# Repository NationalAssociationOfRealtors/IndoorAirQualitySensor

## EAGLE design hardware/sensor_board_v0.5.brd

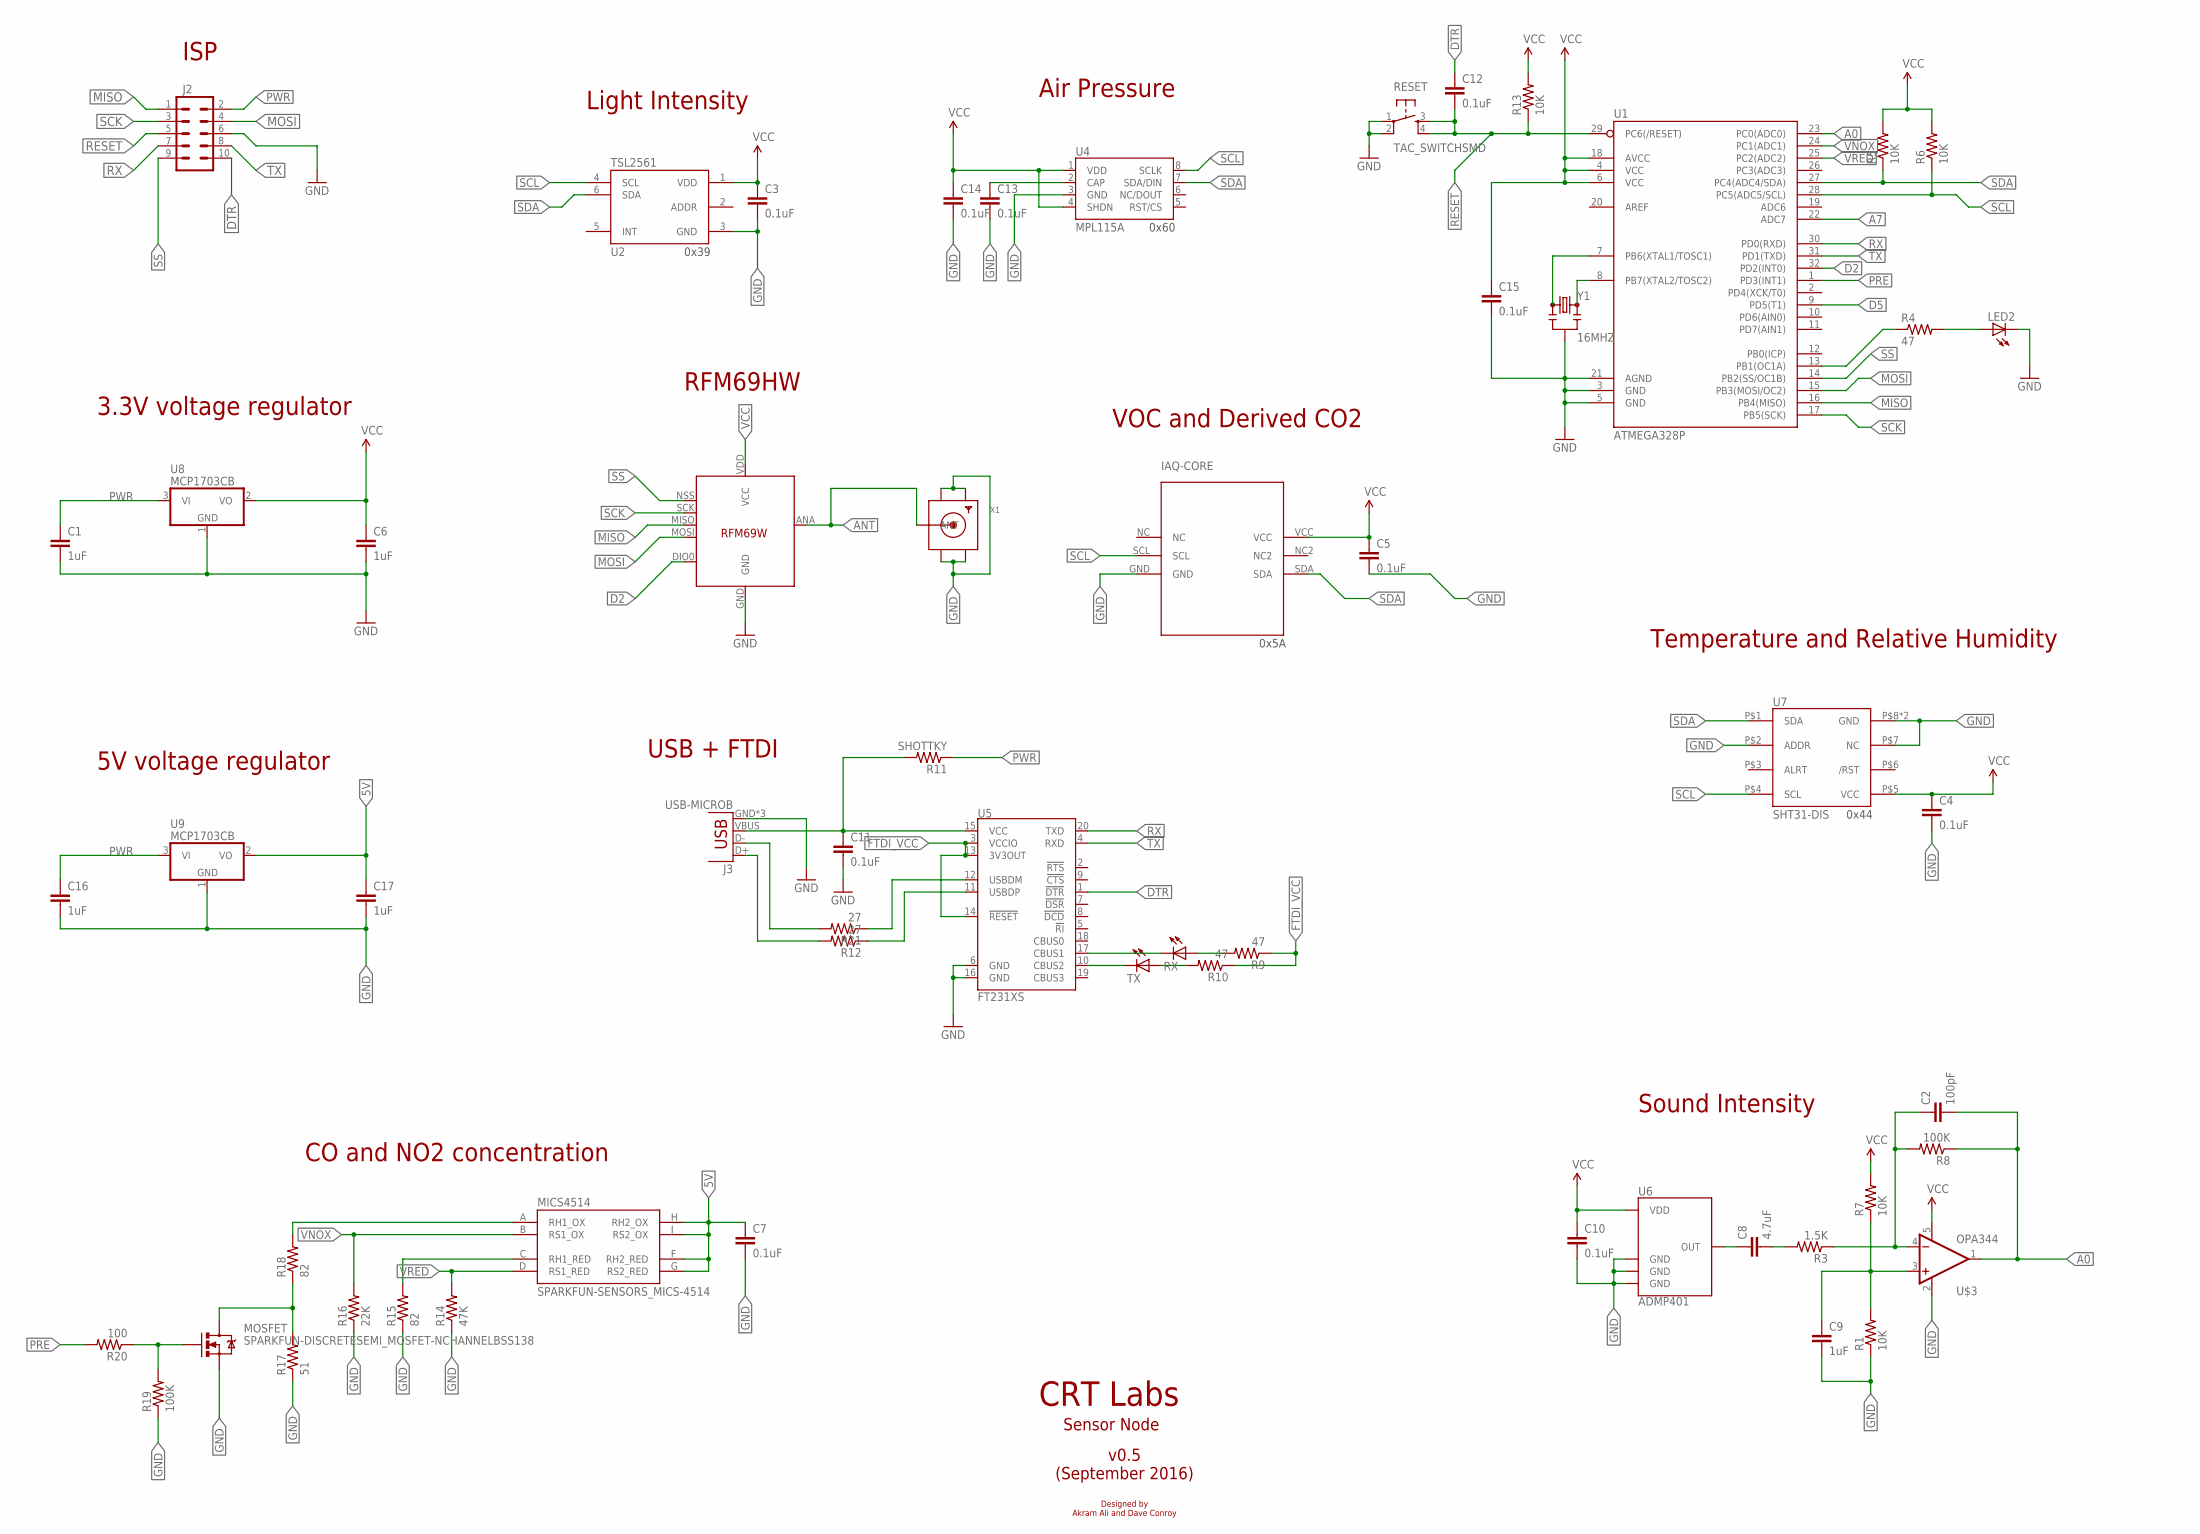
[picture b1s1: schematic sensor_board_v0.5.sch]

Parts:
C1, C6, C9, C16, C17: 1uF; 0805
C2: 100pF; 0805
C3, C4, C5, C7, C10, C11, C12, C13, C14, C15: 0.1uF; 0805
C8: 4.7uF; 0805
IAQ-CORE: IAQ-CORE; MPN IAQ CORE
J2: M05X2PTH; AVR_ICSP
J3: USB-MICROB
LED2: LEDCHIPLED_0805; CHIPLED_0805
MICS4514: SPARKFUN-SENSORS_MICS-4514; SPARKFUN-SENSORS_MICS_10-SMD
MOSFET: SPARKFUN-DISCRETESEMI_MOSFET-NCHANNELBSS138; SPARKFUN-DISCRETESEMI_SOT23-3
R1, R5, R6, R7, R13: 10K; 0805
R3: 1.5K; 0805
R4, R9, R10: 47; 0805
R8, R19: 100K; 0805
R11: SHOTTKY; 0805
R12, R21: 27; 0805
R14: 47K; 0805
R15, R18: 82; 0805
R16: 22K; 0805
R17: 51; 0805
R20: 100; 0805
RESET: TAC_SWITCHSMD; TACTILE-SWITCH-SMD
RX: LEDCHIPLED_0805; CHIPLED_0805
TX: LEDCHIPLED_0805; CHIPLED_0805
U1: ATMEGA328P; TQFP32-08; MPN ATMEGA328PB-AU
U2: TSL2561; FN-6; MOUSER# 856-TSL2561T; DIGIKEY# TSL2561-FNCT-ND
U4: MPL115A; LGA8
U5: FT231XS; SSOP20_L
U6: ADMP401
U7: SHT31-DIS; SHT3X; MPN SHT31-DIS-B
U8, U9: MCP1703CB; SOT23; MPN MCP1703T-2502E/CB
U$3: OPA344; SOT23-5
U$4: RFM69HW; LOWPOWERLAB_RFM69W-MINPADS
X1: SMACONNECTOR_EDGE; SMA_EDGELAUNCH
Y1: 16MHZ; RESONATOR-SMD

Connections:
5V: C7.1, C17.1, MICS4514.F (RH2_RED), MICS4514.G (RS2_RED), MICS4514.H (RH2_OX), MICS4514.J (RS2_OX), U9.2 (VO)
A0: C2.2, R8.1, U1.23 (PC0(ADC0)), U$3.1 (OUT)
A7: U1.22 (ADC7)
ANT: U$4.ANA (ANT), X1.P (ANT)
D2: U1.32 (PD2(INT0)), U$4.DIO0
D5: U1.9 (PD5(T1))
DTR: C12.1, J2.10, U5.1 (!DTR)
FTDI_VCC: R9.1, R10.1, U5.3 (VCCIO), U5.13 (3V3OUT), U5.14 (!RESET)
GND: C1.2, C3.2, C4.2, C5.2, C6.2, C7.2, C9.2, C10.2, C11.2, C13.2, C14.2, C15.2, C16.2, C17.2, IAQ-CORE.GND, J2.6, J3.GND, J3.MT1 (GND), J3.MT2 (GND), LED2.C, MOSFET.2 (S), R1.1, R14.1, R15.1, R16.1, R17.1, R19.1, RESET.1, RESET.2, U1.3 (GND), U1.5 (GND), U1.21 (AGND), U2.3 (GND), U4.3 (GND), U5.6 (GND), U5.16 (GND), U6.2 (GND), U6.4 (GND), U6.6 (GND), U7.P$2 (ADDR), U7.P$7 (NC), U7.P$8 (GND), U7.PAD (GND), U8.1 (GND), U9.1 (GND), U$3.2 (V-), U$4.GND, X1.GND@1 (GND4), X1.GND@2 (GND3), X1.GND@3 (GND2), X1.GND@4 (GND1), Y1.2
MISO: J2.1, U1.16 (PB4(MISO)), U$4.MISO
MOSI: J2.4, U1.15 (PB3(MOSI/OC2)), U$4.MOSI
unnamed: R4.1, U1.13 (PB1(OC1A))
unnamed: LED2.A, R4.2
unnamed: U1.8 (PB7(XTAL2/TOSC2)), Y1.3
unnamed: U1.7 (PB6(XTAL1/TOSC1)), Y1.1
unnamed: C8.1, U6.1 (OUT)
unnamed: MICS4514.A (RH1_OX), R18.2
unnamed: C8.2, R3.2
unnamed: C2.1, R3.1, R8.2, U$3.4 (-IN)
unnamed: C9.1, R1.2, R7.1, U$3.3 (+IN)
unnamed: C13.1, U4.2 (CAP)
unnamed: MICS4514.C (RH1_RED), R15.2
unnamed: RX.C, U5.17 (CBUS1)
unnamed: TX.C, U5.10 (CBUS2)
unnamed: MOSFET.3 (D), R17.2, R18.1
unnamed: MOSFET.1 (G), R19.2, R20.1
unnamed: R21.1, U5.12 (USBDM)
unnamed: R12.1, U5.11 (USBDP)
unnamed: R9.2, RX.A
unnamed: R10.2, TX.A
unnamed: J3.D-, R21.2
unnamed: J3.D+, R12.2
PRE: R20.2, U1.1 (PD3(INT1))
PWR: C1.1, C16.1, J2.2, R11.1, U8.3 (VI), U9.3 (VI)
RESET: C12.2, J2.5, R13.1, RESET.3, RESET.4, U1.29 (PC6(/RESET))
RX: J2.7, U1.30 (PD0(RXD)), U5.20 (TXD)
SCK: J2.3, U1.17 (PB5(SCK)), U$4.SCK
SCL: IAQ-CORE.SCL, R6.1, U1.28 (PC5(ADC5/SCL)), U2.4 (SCL), U4.8 (SCLK), U7.P$4 (SCL)
SDA: IAQ-CORE.SDA, R5.1, U1.27 (PC4(ADC4/SDA)), U2.6 (SDA), U4.7 (SDA/DIN), U7.P$1 (SDA)
SS: J2.9, U1.14 (PB2(SS/OC1B)), U$4.NSS (SEL)
TX: J2.8, U1.31 (PD1(TXD)), U5.4 (RXD)
VBUS: C11.1, J3.VBUS, R11.2, U5.15 (VCC)
VCC: C3.1, C4.1, C5.1, C6.1, C10.1, C14.1, C15.1, IAQ-CORE.VCC, R5.2, R6.2, R7.2, R13.2, U1.4 (VCC), U1.6 (VCC), U1.18 (AVCC), U2.1 (VDD), U4.1 (VDD), U4.4 (SHDN), U6.5 (VDD), U7.P$5 (VCC), U8.2 (VO), U$3.5 (V+), U$4.VDD (VCC)
VNOX: MICS4514.B (RS1_OX), R16.2, U1.24 (PC1(ADC1))
VRED: MICS4514.D (RS1_RED), R14.2, U1.25 (PC2(ADC2))

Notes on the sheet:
Light Intensity
VOC and Derived CO2
Air Pressure
Sound Intensity
Temperature and Relative Humidity
ISP
3.3V voltage regulator
CO and NO2 concentration
CRT Labs
Sensor Node
v0.5 (September 2016)
Designed by Akram Ali and Dave Conroy
5V voltage regulator
RFM69HW
USB + FTDI
0x39
0x60
0x5A
0x44

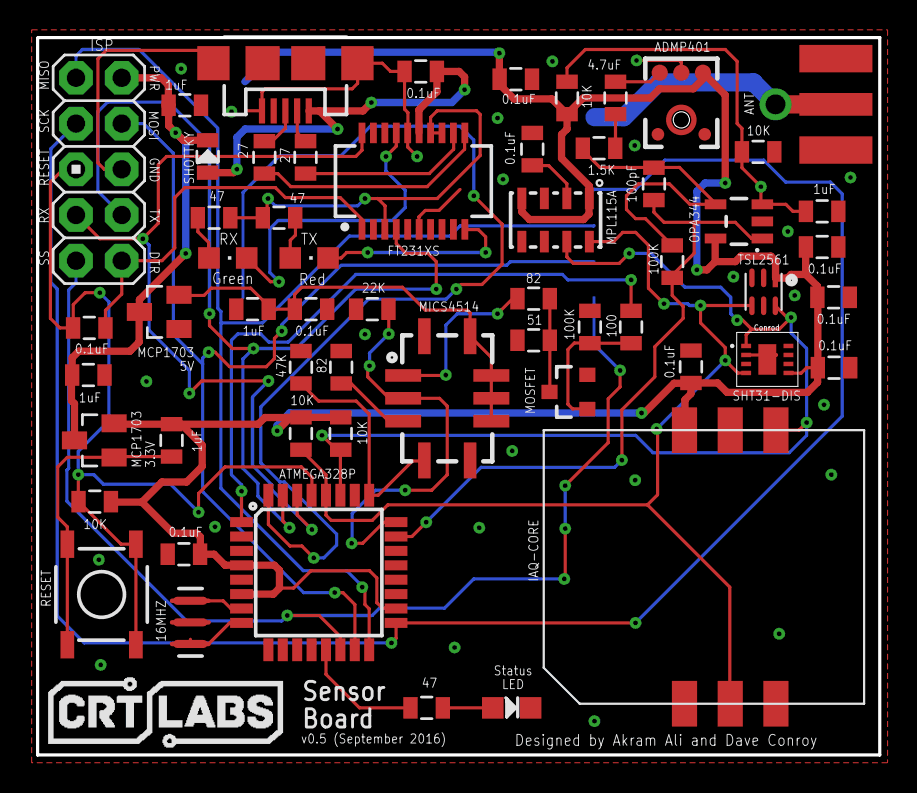
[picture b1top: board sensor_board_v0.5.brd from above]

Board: 2 copper layers, 46.8 x 39.9 mm, 58 parts (1 on the bottom side), 43 nets.

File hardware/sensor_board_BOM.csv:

Qty,Value,Device,Package,Parts,DIGIKEY#,MANF,MANF#,MOUSER#,MPN,OC_NEWARK,PROD_ID,VALUE,Description
1,1.5K,RESISTOR0805-RES,805,R3,YAG1814CT-ND,Yageo,RT0805BRD071K5L,603-RT0805BRD071K5L,RT0805BRD071K5L,unknown,,,Resistor
1,100,RESISTOR0805-RES,805,R20,311-100CRCT-NDE,,RC0805FR-07100RL,603-RC0805FR-07100RL,RC0805FR-07100RL,unknown,,,Resistor
1,100pF,CAP0805,805,C2,311-1111-1-ND,,CC0805JRNPO9BN101,603-CC805JRNPO9BN101,CC0805JRNPO9BN101,unknown,,,Capacitor
1,10K,RESISTOR0805-RES,805,R13,311-10KARCT-ND,Yageo,RC0805JR-0710KL,603-RC0805JR-0710KL,RC0805JR-0710KL,,,,Resistor
1,16MHZ,RESONATOR16MHZ,RESONATOR-SMD,Y1,490-1198-1-ND,,CSTCE16M0V53-R0,81-CSTCE16M0V53-R0,CSTCE16M0V53-R0,unknown,XTAL-08900,16MHZ,Resonator
1,22K,RESISTOR0805-RES,805,R16,311-22KARCT-NDE,,RC0805JR-0722KL,603-RC0805JR-0722KL,RC0805JR-0722KL,unknown,,,Resistor
1,4.7uF,CAP0805,805,C8,311-1871-1-ND,,CC0805KKX5R8BB475,603-CC805KKX5R8BB475,CC0805KKX5R8BB475,unknown,,,Capacitor
1,47K,RESISTOR0805-RES,805,R14,RHM47KKCT-ND,Rohm Semiconductor,ESR10EZPJ473,755-ESR10EZPJ473,ESR10EZPJ473,unknown,,,Resistor
1,51,RESISTOR0805-RES,805,R17,RHM51KCT-ND,Rohm Semiconductor,ESR10EZPJ510,755-ESR10EZPJ510,ESR10EZPJ510,unknown,,,Resistor
1,ADMP401,ADMP401,ADMP401,U6,INMP401ACEZ-R7CT-ND,,INMP401ACEZ-R7,N/A,INMP401ACEZ-R7,,,,Omnidirection bottom-port MEMS microphone
1,ATMEGA328P,ATMEGA328P_TQFP,TQFP32-08,U1,ATMEGA328P-AU-ND,Atmel,ATMEGA328P-AU,556-ATMEGA328P-AU,ATMEGA328P-AU,58Y6083,IC-09069,ATMEGA328P_TQFP,
1,FT231XS,FT231XS,SSOP20_L,U5,768-1129-1-ND,FTDI,FT231XS-R,895-FT231XS-R,FT231XS-R,,IC-11524,FT231XS,FTDI FT231X Full Speed USB to Full-handshake UART
1,IAQ-CORE,IAQ-CORE,IAQ-CORE,IAQ-CORE,IAQ-CORE C-ND,ams,IAQ-CORE C,985-IAQ-COREC,IAQ-CORE C,82Y5455,,,
1,MPL115A,MPL115A,LGA8,U4,MPL115A2-ND,Freescale Semiconductor - NXP,MPL115A2,841-MPL115A2,MPL115A2,,,,MPL115A1 (SPI) and MPL115A2 (I2C) Miniature Digital Barometer
1,OPA344,OPA344,SOT23-5,U$3,296-41475-1-ND,Texas Instruments,OPA344NA/3K,595-OPA344NA/3K,OPA344NA/3K,,IC-08251,,Single gate rail-to-rail output op-amp. Inputs extend 300mV past rails.
,,,,,,,,,,,,,
1,SHOTTKY,RESISTOR0805-RES,805,R11,478-7799-1-ND,AVX,SD0805S020S0R5,581-SD0805S020S0R5,SD0805S020S0R5,unknown,,,Resistor
1,SHT31-DIS,SHT31-DIS,SHT3X,U7,1649-1011-1-ND,,SHT31-DIS-B,403-SHT31-DIS-B,SHT31-DIS-B,47Y1304,,,
1,TAC_SWITCHSMD,TAC_SWITCHSMD,TACTILE-SWITCH-SMD,RESET,CKN9104CT-ND,C&K Components,PTS525SM15SMTR2 LFS,611-PTS525SM15SMTR2,PTS525SM15SMTR2 LFS,,SWCH-08247,TAC_SWITCHSMD,Momentary Switch
1,TSL2561,TSL2561FN,FN-6,U2,TSL2561-FNCT-ND,AMS-TAOS-USA-Inc.,TSL2561FN,856-TSL2561T,TSL2561FN,82Y5564,IC-11791,,TSL2561 illumination sensor
1,USB-MICROB,USB-MICROB,USB-MICROB,J3,,,,,,,CONN-09505,,USB Connectors
2,100K,RESISTOR0805-RES,805,R8,311-100KCRCT-NDE,Yageo,RC0805FR-07100KL,603-RC0805FR-07100KL,RC0805FR-07100KL,,,,
2,27,RESISTOR0805-RES,805,R12,,Yageo,RC0603JR-0727RL,603-RC0603JR-0727RL,RC0603JR-0727RL,,,,
2,82,RESISTOR0805-RES,805,R15,541-82.0CCT-NDE,,CRCW080582R0FKEA,71-CRCW0805-82-E3,CRCW080582R0FKEA,,,,
2,MCP1703CB,MCP1703CB,SOT23,U8,MCP1703T-3302E/CBCT-ND,,MCP1703T-3302E/CB,579-MCP1703T-3302ECB,MCP1703T-3302E/CB,,,,
3,,LEDCHIPLED_0805,CHIPLED_0805,LED2,LED,LED,LED,LED,LED,LED,LED,LED,LED
3,47,RESISTOR0805-RES,805,R4,311-47ARCT-ND,,RC0805JR-0747RL,603-RC0805JR-0747RL,RC0805JR-0747RL,,,,
4,0.1uF,CAP0805,805,C12,311-1088-1-ND,,CC0603KRX7R7BB104,603-CC603KRX7R7BB104,CC0603KRX7R7BB104,,,,
4,10K,RESISTOR0805-RES,805,R1,311-10KARCT-ND,Yageo,RC0805JR-0710KL,603-RC0805JR-0710KL,RC0805JR-0710KL,,,,
5,1uF,CAP0805,805,C1,311-1365-1-ND,,CC0805KKX7R7BB105,603-CC805KKX7R7BB105,CC0805KKX7R7BB105,,,,
6,0.1uF,CAP0805,805,C3,311-1088-1-ND,,CC0603KRX7R7BB104,603-CC603KRX7R7BB104,CC0603KRX7R7BB104,,,,
,,,,,,,,,,,,,
,,,,,,,,,,,,,
,,,,,,,,,,,,,
Optional,,,,,,,,,,,,,
1,,M05X2PTH,AVR_ICSP,J2,,,,,0,,,,Header 5x2
1,,SMACONNECTOR_EDGE,SMA_EDGELAUNCH,X1,,,,,,,,,SMA Connector
1,SPARKFUN-DISCRETESEMI_MOSFET-NCHANNELBSS138,SPARKFUN-DISCRETESEMI_MOSFET-NCHANNELBSS138,SPARKFUN-DISCRETESEMI_SOT23-3,MOSFET,,,,,,,TRANS-00830,,Common NMOSFET Parts
1,SPARKFUN-SENSORS_MICS-4514,SPARKFUN-SENSORS_MICS-4514,SPARKFUN-SENSORS_MICS_10-SMD,MICS4514,,,,,,,COMP-12310,,Metal oxide MEMS carbon monoxide (CO) and NOx sensor in an SMD package.
1,RFM69HW,LOWPOWERLAB_RFM69,LOWPOWERLAB_RFM69W-MINPADS,U$4,,,,,,,,,

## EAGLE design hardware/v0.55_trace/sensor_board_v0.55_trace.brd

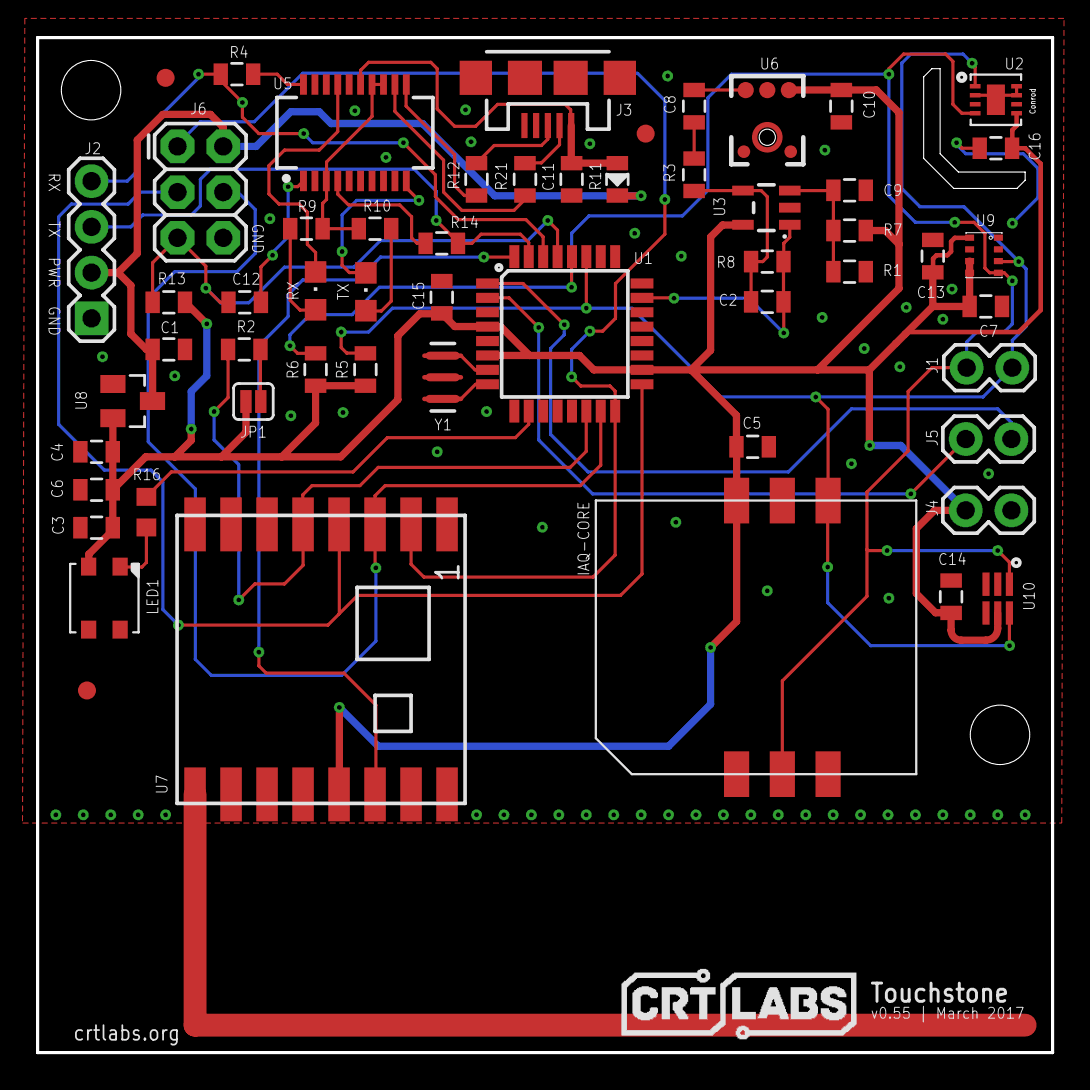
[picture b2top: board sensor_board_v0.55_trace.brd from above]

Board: 2 copper layers, 56.4 x 56.4 mm, 58 parts (0 on the bottom side), 38 nets.

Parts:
C1, C3, C9: 1uF; 0805
C2: 100pF; 0805
C4: 10uF; 0805
C5, C6, C7, C10, C11, C12, C13, C14, C15, C16: 0.1uF; 0805
C8: 4.7uF; 0805
H1, H2: STAND-OFF
IAQ-CORE: IAQ-CORE
J1, J4, J5: 1X02
J2: 1X04
J3: USB-MICROB
J6: AVR_SPI_PRG_6PTH; 2X3
JP1: JUMPER-PAD-2-NC_BY_PASTEFULL-BOX-SILK; PAD-JUMPER-2-NC_BY_PASTE_YES_SILK_FULL_BOX
LED1: WS2812B3535; LED3535
R1, R2, R5, R6, R7, R13: 10K; 0805
R3: 1.5K; 0805
R4, R14: 1K; 0805
R8: 100K; 0805
R9, R10: 47; 0805
R11: SHOTTKY; 0805
R12, R21: 27; 0805
R16: 470; R0603
RX: CHIPLED_0805
TX: CHIPLED_0805
U1: ATMEGA328P; TQFP32-08
U2: SHT35; SHT3X
U3: OPA344; SOT23-5
U5: FT231XS; SSOP20_L
U6: ADMP401
U7: RFM69HCW; RFM69HCW-XXXS2
U8: MCP1703CB; SOT23
U9: BMP280
U10: TSL2591; DFN6_TAOS
U$1, U$2, U$3: FIDUCIAL; FIDUCIAL_1MM
Y1: 16MHZ; RESONATOR-SMD

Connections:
A0: C2.2, R8.1, U1.23, U3.1
D2: U1.32, U7.14
D3: J5.2, U1.1
D4: J5.1, U1.2
D6: R16.2, U1.10
DTR: C12.1, U5.1
FTDI_VCC: R9.1, R10.1, U5.3, U5.13, U5.14
GND: C1.2, C3.2, C4.2, C5.2, C6.2, C7.2, C9.2, C10.2, C11.2, C13.2, C14.1, C15.2, C16.2, IAQ-CORE.GND, J2.1, J3.GND, J3.MT1, J3.MT2, J4.1, J6.6, LED1.4, R1.1, U1.3, U1.5, U1.21, U2.2, U2.7, U2.8, U2.THERMAL, U3.2, U5.6, U5.16, U6.2, U6.4, U6.6, U7.1, U7.8, U7.10, U8.1, U9.1, U9.7, U10.3, Y1.2
MISO: J6.1, U1.16, U7.2
MOSI: J6.4, U1.15, U7.3
unnamed: JP1.1, R2.2
unnamed: R14.2, U5.4
unnamed: R4.2, U5.20
unnamed: U1.8, Y1.3
unnamed: U1.7, Y1.1
unnamed: LED1.1, R16.1
unnamed: C8.2, R3.2
unnamed: C2.1, R3.1, R8.2, U3.4
unnamed: C9.1, R1.2, R7.1, U3.3
unnamed: RX.C, U5.17
unnamed: TX.C, U5.10
unnamed: R21.1, U5.12
unnamed: R12.1, U5.11
unnamed: R9.2, RX.A
unnamed: R10.2, TX.A
unnamed: J3.D-, R21.2
unnamed: J3.D+, R12.2
OUT: C8.1, U6.1
PWR: C1.1, J2.2, J6.2, R11.1, U8.3
RESET: C12.2, J6.5, R13.1, U1.29
RX: J2.4, R4.1, U1.30
SCK: J6.3, U1.17, U7.4
SCL: IAQ-CORE.SCL, J1.1, R6.1, U1.28, U2.4, U9.4, U10.1
SDA: IAQ-CORE.SDA, J1.2, R5.1, U1.27, U2.1, U9.3, U10.6
SS: R2.1, U1.14, U7.5
TX: J2.3, R14.1, U1.31
VBUS: C11.1, J3.VBUS, R11.2, U5.15
VCC: C3.1, C4.1, C5.1, C6.1, C7.1, C10.1, C13.1, C14.2, C15.1, C16.1, IAQ-CORE.VCC, J4.2, JP1.2, LED1.2, R5.2, R6.2, R7.2, R13.2, U1.4, U1.6, U1.18, U2.5, U3.5, U6.5, U7.13, U8.2, U9.5, U9.6, U9.8, U10.5

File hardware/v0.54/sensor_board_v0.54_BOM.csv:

Qty,Value,Device,Package,Parts,Description,MPN
1,USB-MICROB,USB-MICROB,USB-MICROB,J3,USB Connectors,47346-0001
1,ATMEGA328P,ATMEGA328P_TQFP,TQFP32-08,U1,ATMEGA328P,ATMEGA328PB-AU
1,BMP280,BMP280,BMP280,U9,The BMP280 is an absolute barometric pressure sensor especially designed for mobile applications. The sensor module is housed in an extremely compact 8-pin metal-lid LGA package with a footprint of only 2.0 ÌÑ 2.5 mm2 and 0.95 mm package height. Its small,BMP280
1,100pF,CAP0805,805,C2,Capacitor,CC0805JRNPOABN101
1,10uF,CAP0805,805,C4,Capacitor,CC0805KKX5R6BB106
1,4.7uF,CAP0805,805,C8,Capacitor,CC0805KKX7R6BB475
10,0.1uF,CAP0805,805,C5-C6-C7-C10-C11-C12-C13-C14-C15-C16,Capacitor,CC0805KRX7R9BB104
3,1uF,CAP0805,805,C1-C3-C9,Capacitor,CC0805ZRY5V8BB105
1,16MHZ,RESONATOR16MHZ,RESONATOR-SMD,Y1,Resonator,CSTCE16M0V53-R0
1,FT231XS,FT231XS,SSOP20_L,U5,FTDI FT231X Full Speed USB to Full-handshake UART,FT231XQ-R
1,IAQ-CORE,IAQ-CORE,IAQ-CORE,IAQ-CORE,IAQ-CORE,IAQ-CORE C
1,ADMP401,ADMP401,ADMP401,U6,Omnidirection bottom-port MEMS microphone,INMP401ACEZ-R7
2,,LEDCHIPLED_0805,CHIPLED_0805,RX- TX,LED,LG R971-KN-1
1,MCP1703CB,MCP1703CB,SOT23,U8,250 mA- 16V- Low Quiescent Current LDO Regulator,MCP1703T-2502E/CB
1,OPA344,OPA344,SOT23-5,U3,Single gate rail-to-rail output op-amp. Inputs extend 300mV past rails.,OPA344NA/3K
1,100K,RESISTOR0805-RES,805,R8,Resistor,RC0805FR-07100KL 
6,10K,RESISTOR0805-RES,805,R1-R2-R5-R6-R7-R13,Resistor,RC0805FR-0710KL
1,1.5K,RESISTOR0805-RES,805,R3,Resistor,RC0805FR-071K5L 
2,1K,RESISTOR0805-RES,805,R4-R14,Resistor,RC0805FR-071KL
2,27,RESISTOR0805-RES,805,R12-R21,Resistor,RC0805FR-0727RL 
1,470,R-US_R0603,R0603,R16,RESISTOR- American symbol,RC0805FR-07470RL 
2,47,RESISTOR0805-RES,805,R9-R10,Resistor,RC0805FR-0747RL 
1,RFM69HW,LOWPOWERLAB_RFM69,LOWPOWERLAB_RFM69W-MINPADS,U4,RFM Radio,RFM69HW
1,SHOTTKY,RESISTOR0805-RES,805,R11,Resistor,SD0805S040S0R5
1,SHT35,SHT3X,SHT3X,U2,SHT3x - Digital Temperature and Humidity Sensor,SHT35-DIS-B
1,WS2812B3535,WS2812B3535,LED3535,LED1,LED,SK6812 mini
1,TSL2591,LIGHT_TSL2591,DFN6_TAOS,U10,TSL2591 Light-To-Digital Sensor,TSL25911FN

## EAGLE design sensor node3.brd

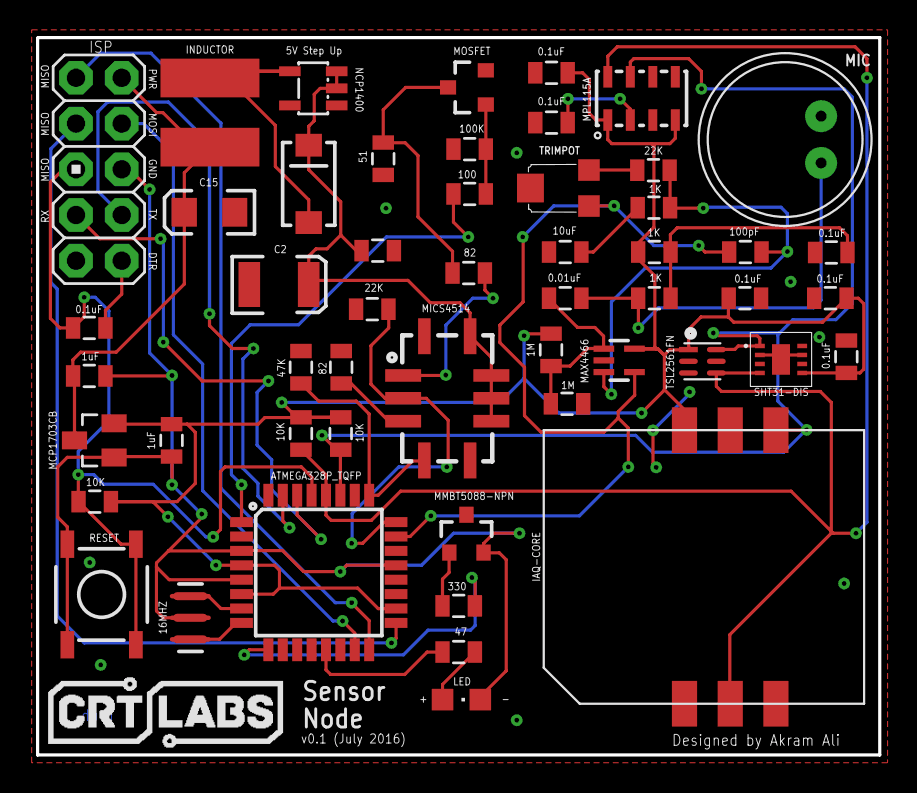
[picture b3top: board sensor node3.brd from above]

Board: 2 copper layers, 46.8 x 39.9 mm, 52 parts (0 on the bottom side), 36 nets.

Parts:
C1, C6: 1uF; 0805
C2: EIA3528
C3, C4, C5, C7, C9, C12, C13, C14: 0.1uF; 0805
C8: 0.01uF; 0805
C10: 10uF; 0805
C11: 100pF; 0805
C15: EIA3216
D1: SMA-DIODE
IAQ-CORE: IAQ-CORE
IC1: MCP1703CB; SOT23
INDUCTOR: CR54
J2: AVR_ICSP
LED2: CHIPLED_0805
MIC: ELECTRET_9.7
MICS4514: SPARKFUN-SENSORS_MICS-4514; SPARKFUN-SENSORS_MICS_10-SMD
MOSFET: SPARKFUN-DISCRETESEMI_MOSFET-NCHANNELBSS138; SPARKFUN-DISCRETESEMI_SOT23-3
NCP1400: SOT23-5
Q1: MMBT5088-NPN; SOT23-3
R2: 330; 0805
R4: 47; 0805
R5, R6, R13: 10K; 0805
R7, R8: 1M; 0805
R9, R10, R11: 1K; 0805
R12, R16: 22K; 0805
R14: 47K; 0805
R15, R18: 82; 0805
R17: 51; 0805
R19: 100K; 0805
R20: 100; 0805
RESET: TAC_SWITCHSMD; TACTILE-SWITCH-SMD
TRIMPOT: TRIMPOT_BOURNS_TC33X-2
U1: ATMEGA328P_TQFP; TQFP32-08
U2: TSL2561FN; FN-6
U3: SC70-5
U4: MPL115A; LGA8
U$1: SHT31-DIS; SHT3X
Y1: 16MHZ; RESONATOR-SMD

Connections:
5V: C2.A, C7.1, D1.C, MICS4514.F, MICS4514.G, MICS4514.H, MICS4514.J, NCP1400.2, NCP1400.3
A0: C11.2, TRIMPOT.1, U1.23, U3.4
D5: R2.1, U1.9
DTR: C12.1, J2.10
GND: C1.2, C6.2, IC1.1, J2.6, LED2.C, Q1.2, RESET.1, RESET.2, U1.3, U1.5, U1.21, Y1.2
GND0: C2.C, C3.2, C4.2, C5.2, C7.2, C9.2, C10.2, C13.2, C14.2, C15.C, IAQ-CORE.GND, MIC.-, MOSFET.2, NCP1400.5, Q1.3, R8.1, R14.1, R15.1, R16.1, R17.1, R19.1, U2.3, U3.2, U4.3, U$1.P$2, U$1.P$7, U$1.P$8, U$1.PAD
MISO: J2.1, U1.16
MOSI: J2.4, U1.15
unnamed: Q1.1, R2.2
unnamed: R4.1, U1.13
unnamed: LED2.A, R4.2
unnamed: U1.8, Y1.3
unnamed: U1.7, Y1.1
unnamed: C8.2, R7.1, R8.2, U3.1
unnamed: C11.1, R11.2, R12.1, U3.3
unnamed: MICS4514.A, R18.2
unnamed: C8.1, MIC.+, R9.1
unnamed: C9.1, R9.2, R10.1
unnamed: C13.1, U4.2
unnamed: MICS4514.C, R15.2
unnamed: C10.1, R11.1
unnamed: R12.2, TRIMPOT.3
unnamed: D1.A, INDUCTOR.P$2, NCP1400.4
unnamed: MOSFET.3, R17.2, R18.1
unnamed: MOSFET.1, R19.2, R20.1
PRE: R20.2, U1.1
PWR: C1.1, C15.A, IC1.3, INDUCTOR.P$1, J2.2
RESET: C12.2, J2.5, R13.1, RESET.3, RESET.4, U1.29
RX: J2.7, U1.30
SCK: J2.3, U1.17
SCL: IAQ-CORE.SCL, R6.1, U1.28, U2.4, U4.8, U$1.P$4
SDA: IAQ-CORE.SDA, R5.1, U1.27, U2.6, U4.7, U$1.P$1
TX: J2.8, U1.31
VCC: C3.1, C4.1, C5.1, C6.1, C14.1, IAQ-CORE.VCC, IC1.2, R5.2, R6.2, R7.2, R10.2, R13.2, U1.4, U1.6, U1.18, U2.1, U3.5, U4.1, U4.4, U$1.P$5
VNOX: MICS4514.B, R16.2, U1.24
VRED: MICS4514.D, R14.2, U1.25

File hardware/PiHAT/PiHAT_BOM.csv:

Qty,Value,Device,Package,Parts,Description,DIGIKEY#,MANF,MANF#,MF,MOUSER#,MPN,OC_NEWARK,PROD_ID,VALUE
1,,LEDCHIPLED_0805,CHIPLED_0805,LED2,LED,475-1196-1-ND,,,,,,unknown,,
1,,M05X2PTH,AVR_ICSP,J2,Header 5x2,S6105-ND,,,,,,,,
9,0.1uF,CAP0805,805,C3,,311-1088-1-ND,,,,,,,,
1,1.5K,RESISTOR0805-RES,805,R3,Resistor,YAG1814CT-ND,,,,,,,,
1,100,RESISTOR0805-RES,805,R20,Resistor,311-100CRCT-ND,,,,,,,,
1,100K,RESISTOR0805-RES,805,R19,Resistor,311-100KCRCT-ND,,,,,,,,
1,100K,RESISTOR0805-RES,805,R8,Resistor,541-82.0CCT-ND,,,,,,,,
1,100pF,CAP0805,805,C2,Capacitor,311-1111-1-ND,,,,,,,,
5,10K,RESISTOR0805-RES,805,R1,,311-10KARCT-ND,,,,,,,,
1,16MHZ,RESONATOR16MHZ,RESONATOR-SMD,Y1,Resonator,490-1198-1-ND,,,,,,unknown,XTAL-08900,16MHZ
1,1uF,CAP0805,805,C9,Capacitor,311-1365-1-ND,,,,,,,,
1,22K,RESISTOR0805-RES,805,R16,Resistor,311-22KARCT-ND,,,,,,unknown,,
1,4.7uF,CAP0805,805,C8,Capacitor,311-1871-1-ND,,,,,,,,
1,47,RESISTOR0805-RES,805,R4,Resistor,311-47ARCT-ND,,,,,,unknown,,
1,47K,RESISTOR0805-RES,805,R14,Resistor,RHM47KKCT-ND,,,,,,unknown,,
1,51,RESISTOR0805-RES,805,R17,Resistor,RHM51KCT-ND,,,,,,,,
2,82,RESISTOR0805-RES,805,R15,,541-82.0CCT-ND,,,,,,,,
1,ADMP401,ADMP401,ADMP401,U6,Omnidirection bottom-port MEMS microphone,INMP401ACEZ-R7CT-ND,,,,,,,,
1,ATMEGA328P,ATMEGA328P_TQFP,TQFP32-08,U1,,ATMEGA328P-AU-ND,,,,,ATMEGA328PB-AU,58Y6083,IC-09069,ATMEGA328P_TQFP
1,IAQ-CORE,IAQ-CORE,IAQ-CORE,IAQ-CORE,,IAQ-CORE C-ND,,,,,IAQ CORE,82Y5455,,
1,MPL115A,MPL115A,LGA8,U4,MPL115A1 (SPI) and MPL115A2 (I2C) Miniature Digital Barometer,MPL115A2-ND,,,,,,,,
1,OPA344,OPA344,SOT23-5,U3,Single gate rail-to-rail output op-amp. Inputs extend 300mV past rails.,296-41475-1-ND,,,,,,,IC-08251,
1,RASPBERRYPI_BPLUS_HATSLOTS,RASPBERRYPI_BPLUS_HATSLOTS,PI_HAT_SLOTS,RPI1,,,,,,,,,,
1,SHT31-DIS,SHT31-DIS,SHT3X,U7,,1649-1011-1-ND,,,,,SHT31-DIS-B,47Y1304,,
1,SPARKFUN-DISCRETESEMI_MOSFET-NCHANNELBSS138,SPARKFUN-DISCRETESEMI_MOSFET-NCHANNELBSS138,SPARKFUN-DISCRETESEMI_SOT23-3,MOSFET,Common NMOSFET Parts,BSS138-FDICT-ND,,,,,,,TRANS-00830,
1,SPARKFUN-SENSORS_MICS-4514,SPARKFUN-SENSORS_MICS-4514,SPARKFUN-SENSORS_MICS_10-SMD,MICS4514,Metal oxide MEMS carbon monoxide (CO) and NOx sensor in an SMD package.,,,,,,,,COMP-12310,
1,TAC_SWITCHSMD,TAC_SWITCHSMD,TACTILE-SWITCH-SMD,RESET,Momentary Switch,CKN9104CT-ND,,,,,,,SWCH-08247,TAC_SWITCHSMD
1,TSL2561,TSL2561FN,FN-6,U2,TSL2561 illumination sensor,TSL2561-FNCT-ND,AMS-TAOS-USA-Inc.,TSL2561FN,,856-TSL2561T,TSL2561FN,82Y5564,IC-11791,

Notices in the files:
parts and their libraries:
SparkFun-DigitalIC: Licensing: Creative Commons ShareAlike 4.0 International - https://creativecommons.org/licenses/by-sa/4.0
